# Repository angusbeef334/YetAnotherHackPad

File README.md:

# YetAnotherHackPad
A macro pad (hackpad) that I made for the Hack Club [Highway](https://highway.hackclub.com) event.

## Features
9 inputs (MX switches)\
0.91" OLED display\
Powered by Seeed Studio XIAO RP2040\

Render\

Schematic\

PCB design\

Case\

## BOM
1x XIAO RP2040
9x Cherry MX switches
9x 1N4148 THT diodes
1x SK6812 MINI LED
1x SSD1306 OLED panel

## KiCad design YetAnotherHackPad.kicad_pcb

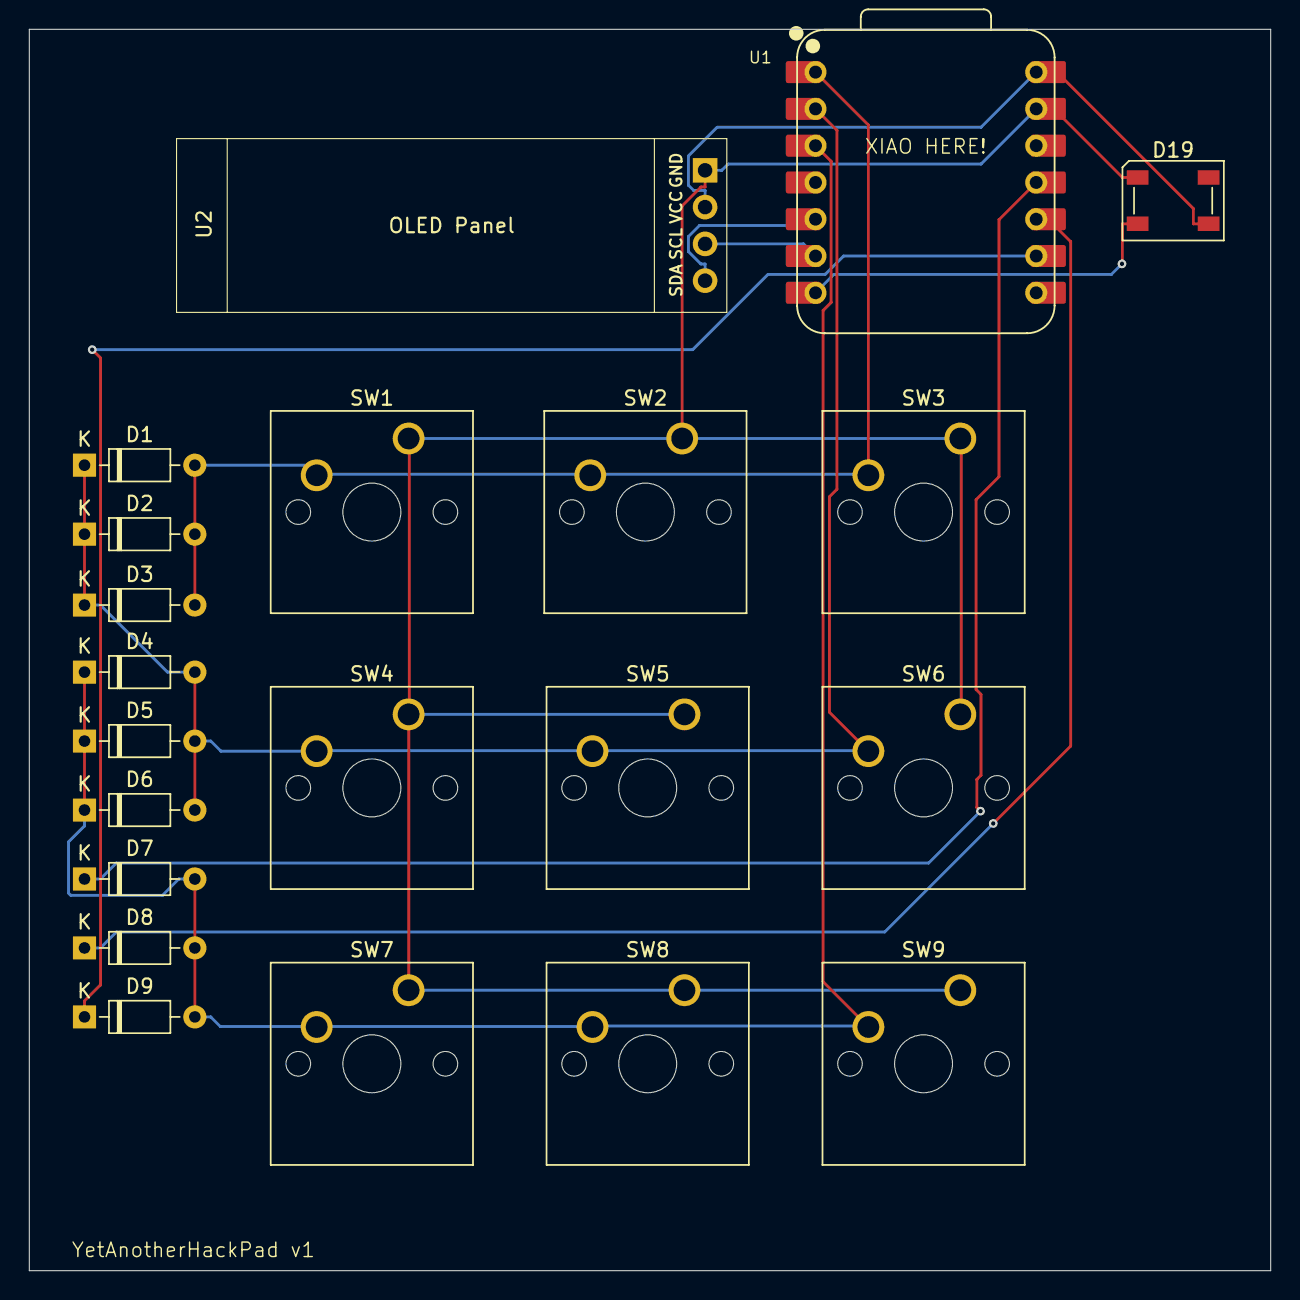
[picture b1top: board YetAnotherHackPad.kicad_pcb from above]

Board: 2 copper layers, 85.7 x 85.7 mm, 21 parts (0 on the bottom side), 11 nets.

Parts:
D1, D2, D3, D4, D5, D6, D7, D8, D9: D; D_DO-35_SOD27_P7.62mm_Horizontal
D19: SK6812; LED_SK6812_PLCC4_5.0x5.0mm_P3.2mm
SW1, SW2, SW3, SW4, SW5, SW6, SW7, SW8, SW9: SW_Push; SW_Cherry_MX_1.00u_PCB
U1: XIAO-RP2040-DIP
U2: SSD1306; SSD1306-0.91-OLED-4pin-128x32

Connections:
+5V: D19.3 (VDD), U1.14 (VBUS), U2.2 (VCC)
GND: D19.1 (VSS), SW1.1, SW2.1, SW3.1, SW4.1, SW5.1, SW6.1, SW7.1, SW8.1, SW9.1, U1.13 (GND), U2.1 (VSS)
unnamed: D1.2 (A), D2.2 (A), D3.2 (A), SW1.2, SW2.2, SW3.2, U1.1 (GPIO26/ADC0/A0)
unnamed: D1.1 (K), D2.1 (K), D3.1 (K), D4.2 (A), D5.2 (A), D6.2 (A), SW4.2, SW5.2, SW6.2, U1.2 (GPIO27/ADC1/A1)
unnamed: D4.1 (K), D5.1 (K), D6.1 (K), D7.2 (A), D8.2 (A), D9.2 (A), SW7.2, SW8.2, SW9.2, U1.3 (GPIO28/ADC2/A2)
unnamed: D7.1 (K), U1.11 (GPIO3/MOSI)
unnamed: D8.1 (K), U1.10 (GPIO4/MISO)
unnamed: D9.1 (K), U1.9 (GPIO2/SCK)
unnamed: D19.2 (DIN), U1.7 (GPIO0/TX)
unnamed: U1.5 (GPIO6/SDA), U2.4 (SDA)
unnamed: U1.6 (GPIO7/SCL), U2.3 (SCL)

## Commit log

2025-07-24 Update README.md
    fix the link formatting
2025-07-25 Update README.md
    fix formatting, link
2025-07-29 remove unneccesary diodes
2025-07-29 restructure
2025-07-29 add firmware and production folders
2025-07-30 add case files
2025-07-30 add gerbers
2025-07-30 add assembly file
